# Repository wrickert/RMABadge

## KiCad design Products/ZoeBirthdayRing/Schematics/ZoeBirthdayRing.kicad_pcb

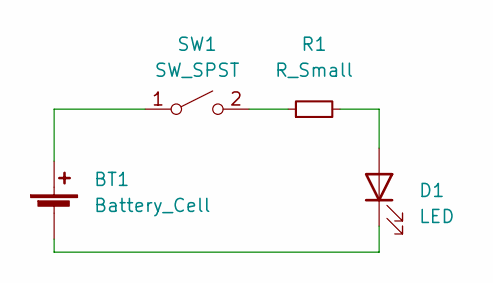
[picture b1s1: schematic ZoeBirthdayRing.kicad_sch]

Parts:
BT1: Battery_Cell; CR2032-MY-2032-12
D1: LED; RGBFlashLED
R1: R_Small; R_0805_2012Metric
SW1: SW_SPST; SW_SPDT_PCM12

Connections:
unnamed: BT1.1 (+), SW1.1 (A)
unnamed: BT1.2 (-), D1.1 (K)
unnamed: D1.2 (A), R1.2
unnamed: R1.1, SW1.2 (B)

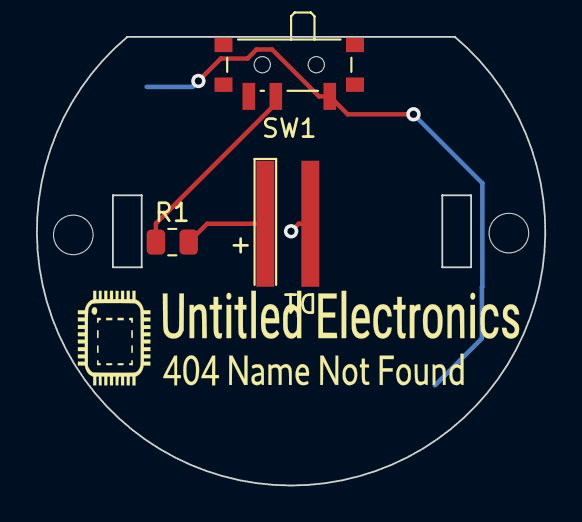
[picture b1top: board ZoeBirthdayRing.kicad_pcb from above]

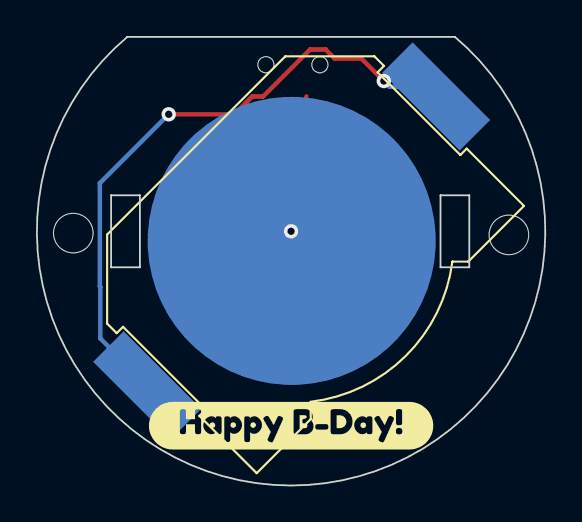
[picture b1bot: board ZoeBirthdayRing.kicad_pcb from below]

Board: 2 copper layers, 28.2 x 24.9 mm, 6 parts (2 on the bottom side), 4 nets.

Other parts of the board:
Ref**: Val**; UELogoSmall
kibuzzard-636FCE78: G***; kibuzzard-636FCE78

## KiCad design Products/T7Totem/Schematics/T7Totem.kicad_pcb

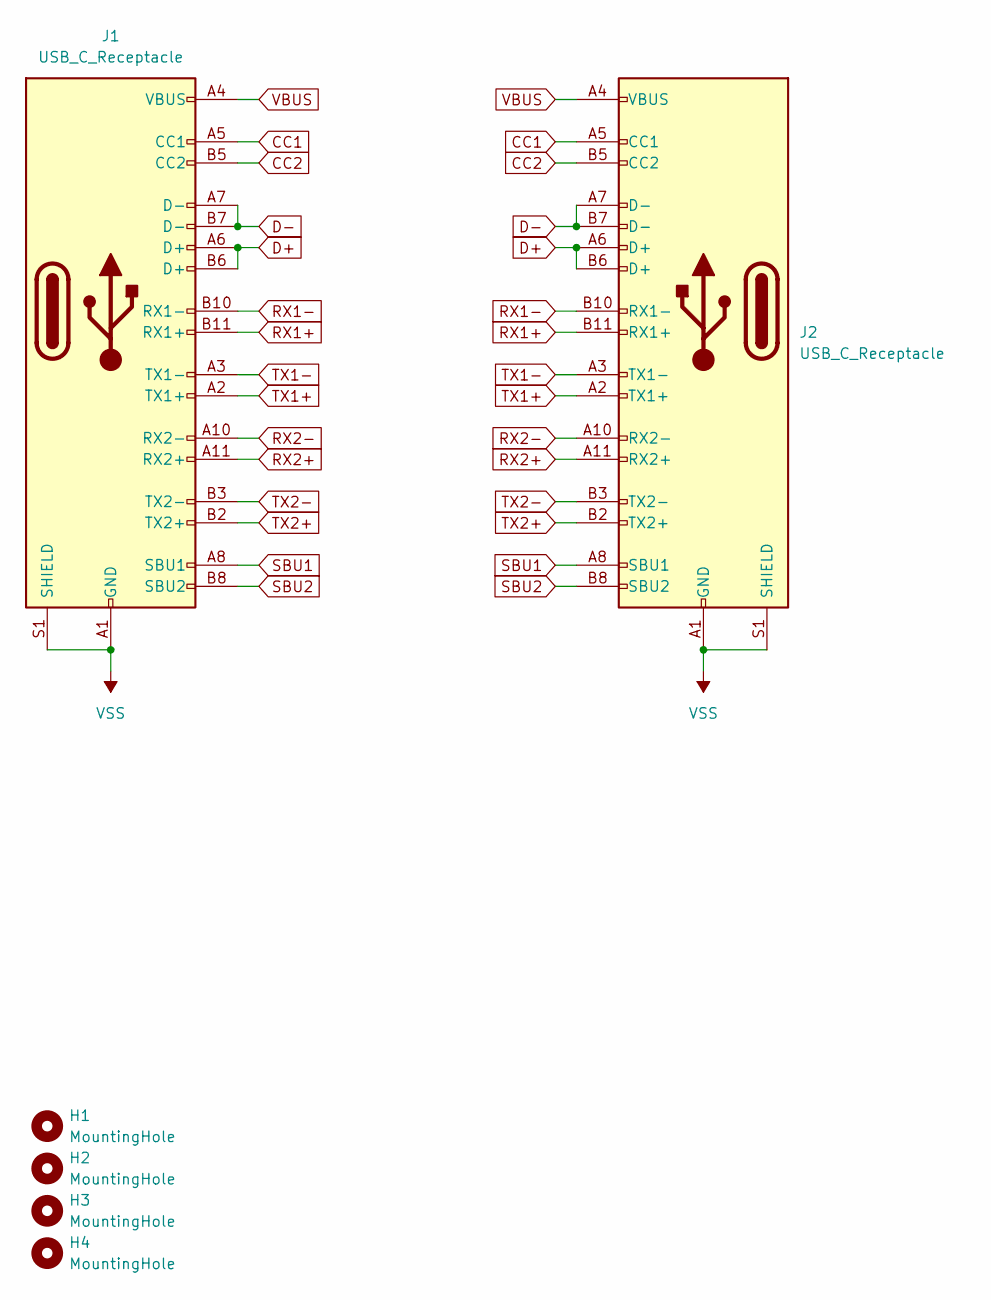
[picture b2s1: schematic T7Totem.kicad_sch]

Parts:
H1, H2, H3, H4: MountingHole; MountingHole_3.2mm_M3
J1: USB_C_Receptacle; U263-241N-4BQC15 Male USBC
J2: USB_C_Receptacle; TYPEC-324-BCP24 USBC Female

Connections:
CC1: J1.A5 (CC1), J2.A5 (CC1)
CC2: J1.B5 (CC2), J2.B5 (CC2)
D+: J1.A6 (D+), J1.B6 (D+), J2.A6 (D+), J2.B6 (D+)
D-: J1.A7 (D-), J1.B7 (D-), J2.A7 (D-), J2.B7 (D-)
RX1+: J1.B11 (RX1+), J2.B11 (RX1+)
RX1-: J1.B10 (RX1-), J2.B10 (RX1-)
RX2+: J1.A11 (RX2+), J2.A11 (RX2+)
RX2-: J1.A10 (RX2-), J2.A10 (RX2-)
SBU1: J1.A8 (SBU1), J2.A8 (SBU1)
SBU2: J1.B8 (SBU2), J2.B8 (SBU2)
TX1+: J1.A2 (TX1+), J2.A2 (TX1+)
TX1-: J1.A3 (TX1-), J2.A3 (TX1-)
TX2+: J1.B2 (TX2+), J2.B2 (TX2+)
TX2-: J1.B3 (TX2-), J2.B3 (TX2-)
VBUS: J1.A4 (VBUS), J1.A9 (VBUS), J1.B4 (VBUS), J1.B9 (VBUS), J2.A4 (VBUS), J2.A9 (VBUS), J2.B4 (VBUS), J2.B9 (VBUS)
VSS: J1.A1 (GND), J1.A12 (GND), J1.B1 (GND), J1.B12 (GND), J1.S1 (SHIELD), J2.A1 (GND), J2.A12 (GND), J2.B1 (GND), J2.B12 (GND), J2.S1 (SHIELD)

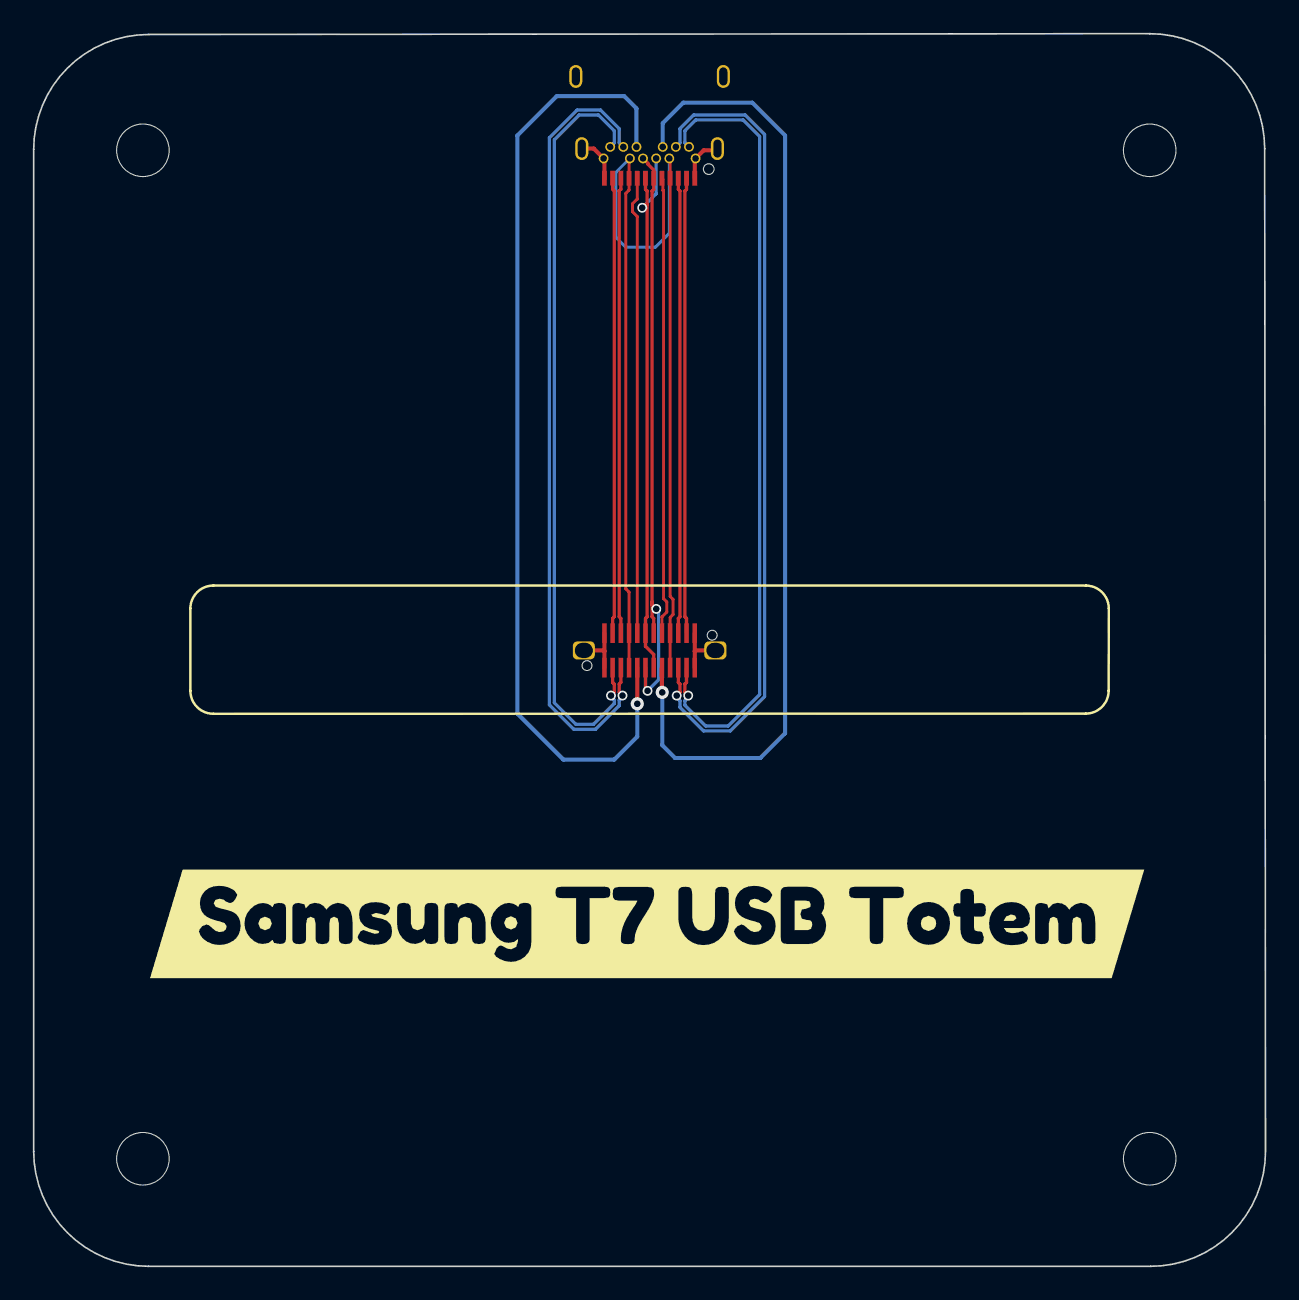
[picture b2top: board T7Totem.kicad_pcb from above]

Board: 4 copper layers, 75.0 x 75.1 mm, 7 parts (0 on the bottom side), 16 nets.

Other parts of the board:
kibuzzard-63322C6E: G***; kibuzzard-63322C6E

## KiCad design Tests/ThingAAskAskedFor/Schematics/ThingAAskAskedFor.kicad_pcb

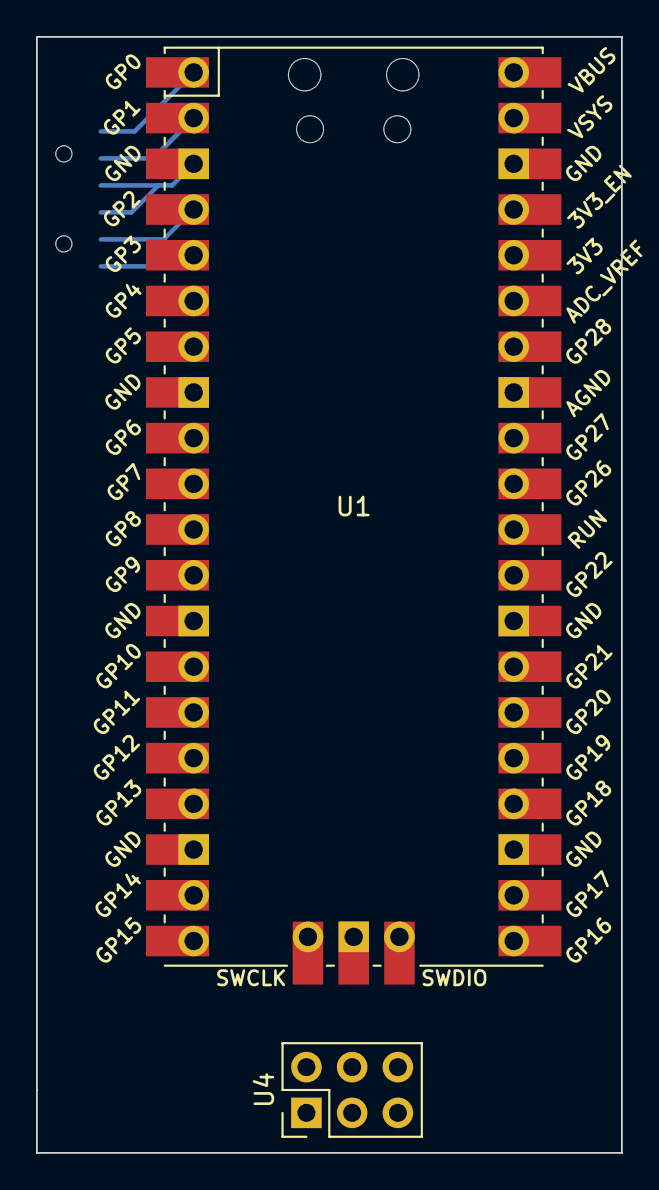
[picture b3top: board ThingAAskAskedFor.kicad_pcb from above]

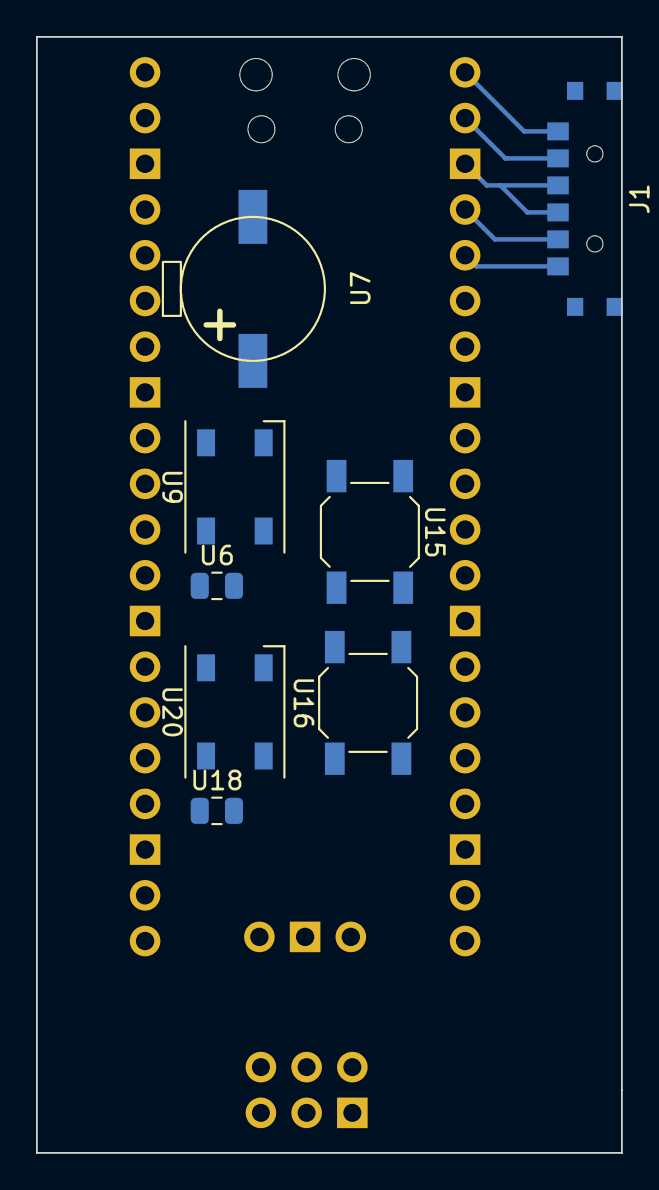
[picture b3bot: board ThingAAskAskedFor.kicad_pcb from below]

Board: 2 copper layers, 32.5 x 62.0 mm, 10 parts (8 on the bottom side), 9 nets.

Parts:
J1: Conn_01x06; MK-14C01-G2 SP4T Switch
U1: Pico; RPi_Pico_SMD_TH
U4: Conn_02x03_Odd_Even; PinHeader_2x03_P2.54mm_Vertical
U6, U18: 100nF; C_0805_2012Metric
U7: Buzzer; FUET-9032-Buzzer
U9, U20: SK6812; LED_SK6812_PLCC4_5.0x5.0mm_P3.2mm
U15, U16: SW_Push; SW_SPST_SKQG_WithoutStem

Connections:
1: J1.6, U1.1 (GPIO0)
2: J1.5, U1.2 (GPIO1)
3: J1.2, U1.4 (GPIO2)
4: J1.1, U1.5 (GPIO3)
Button1: U1.6 (GPIO4), U15.1
Button2: U1.7 (GPIO5), U16.1
unnamed: U9.4 (DOUT), U20.2 (DIN)
VCC: U4.2, U6.1, U9.3 (VDD), U18.1, U20.3 (VDD)
VSS: J1.3, J1.4, U1.3 (GND), U1.8 (GND), U1.13 (GND), U1.18 (GND), U1.23 (GND), U1.28 (GND), U1.33 (AGND), U1.38 (GND), U1.42 (GND), U4.1, U6.2, U7.2 (+), U9.1 (VSS), U15.2, U16.2, U18.2, U20.1 (VSS)

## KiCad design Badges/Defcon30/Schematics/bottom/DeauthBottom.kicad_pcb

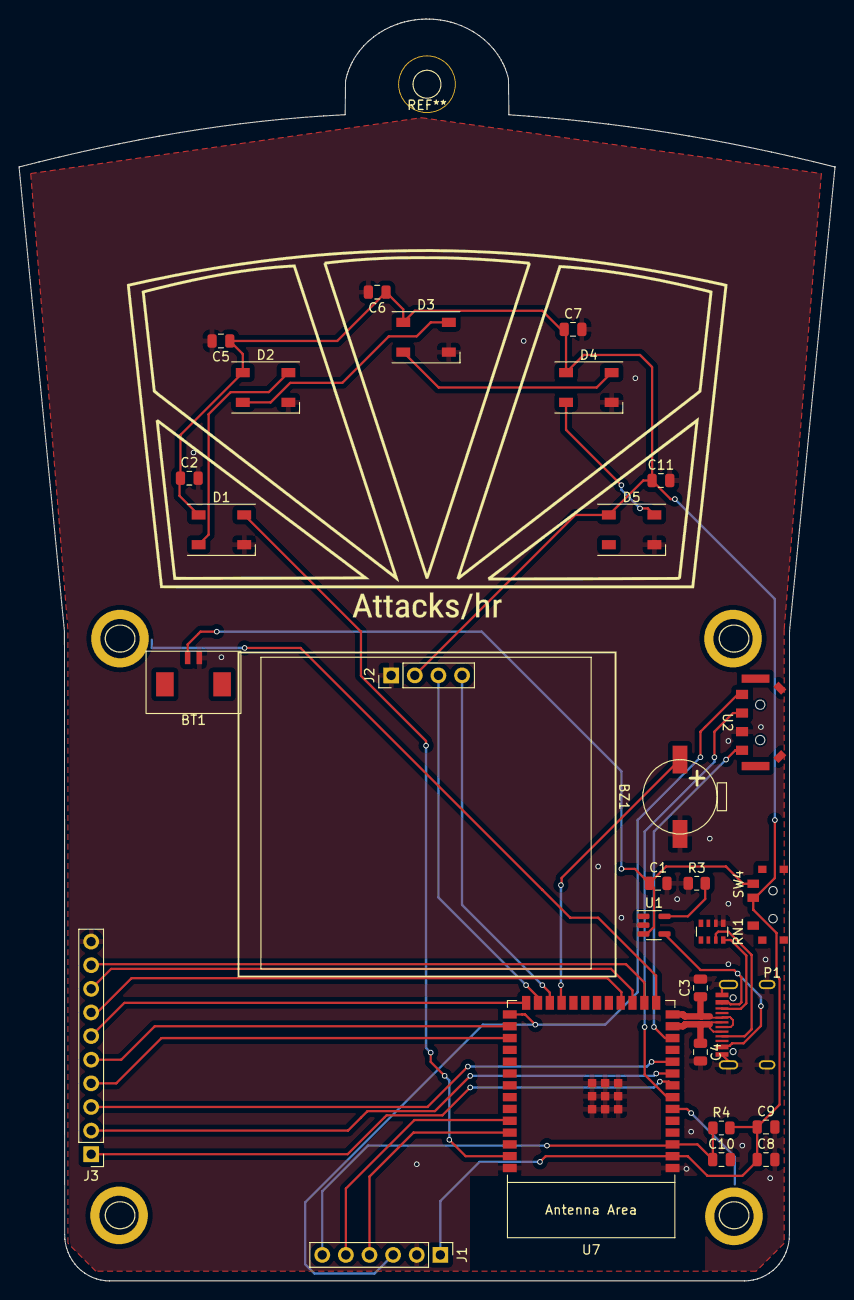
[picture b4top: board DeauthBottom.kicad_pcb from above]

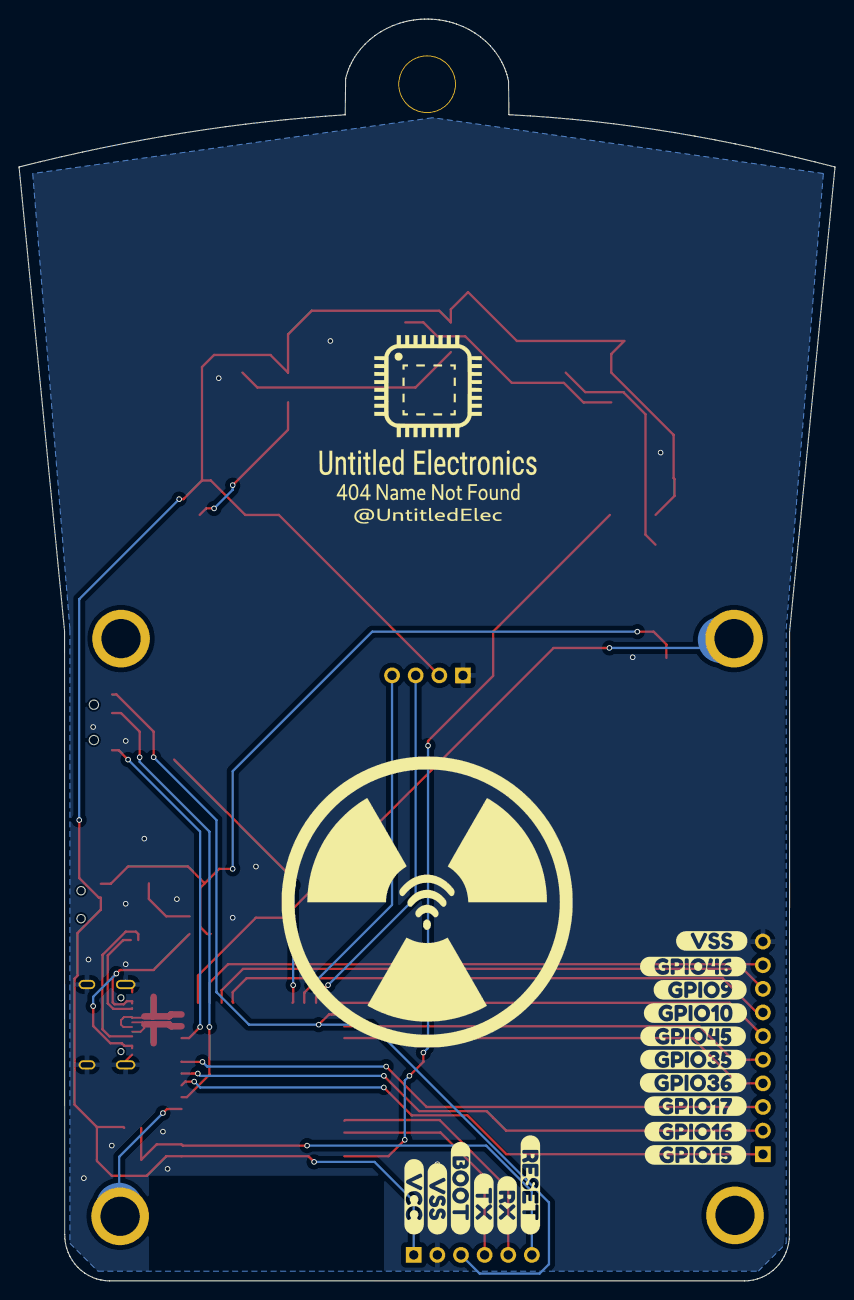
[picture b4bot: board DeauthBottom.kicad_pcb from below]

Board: 2 copper layers, 87.7 x 135.7 mm, 53 parts (20 on the bottom side), 33 nets.

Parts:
BT1: Battery_Cell; AFC12-S02DCC-00
BZ1: Buzzer; FUET-9032-Buzzer
C1: 10uF; C_0805_2012Metric
C2, C5, C6, C7, C9, C10, C11: 100nF; C_0805_2012Metric
C3, C4: 20pF; C_0805_2012Metric
C8: 22uF; C_0805_2012Metric
D1, D2, D3, D4, D5: SK6812; LED_SK6812_PLCC4_5.0x5.0mm_P3.2mm
J1: Program; PinHeader_1x06_P2.54mm_Vertical
J2: Oled Display; Oled
J3: Conn_01x10; PinHeader_1x10_P2.54mm_Vertical
J5, J6, J7, J8: Conn_01x01; SMD Spacer M2.5
J10, J13: Cap Sense; CapSense
P1: USB_C_Plug_corrected; USB_C_Receptical-Jing
R3: 2.5k; R_0805_2012Metric
R4: 1k; R_0805_2012Metric
RN1: 5.1k; R_Array_Convex_4x0603
Ref**: Val**; UELogoAbove
Ref**#2: Val**; wifiRadiation
SW4: SW_SPDT; SK-3296S_switch
U1: HX4055M; SOT-23-5
U2: TM-2023
U7: ESP32-S2-SOLO
kibuzzard-629CC9A4: G***; kibuzzard-629CC9A4
kibuzzard-629CC9AE: G***; kibuzzard-629CC9AE
kibuzzard-629CC9B7: G***; kibuzzard-629CC9B7
kibuzzard-629CC9C0: G***; kibuzzard-629CC9C0
kibuzzard-629CC968: G***; kibuzzard-629CC968
kibuzzard-629CC972: G***; kibuzzard-629CC972
kibuzzard-629CFC39: G***; kibuzzard-629CFC39
kibuzzard-629D3ABB: G***; kibuzzard-629D3ABB
kibuzzard-629D3AC7: G***; kibuzzard-629D3AC7
kibuzzard-629D3AD2: G***; kibuzzard-629D3AD2
kibuzzard-629D3AE1: G***; kibuzzard-629D3AE1
kibuzzard-629D3AEB: G***; kibuzzard-629D3AEB
kibuzzard-629D3AFA: G***; kibuzzard-629D3AFA
kibuzzard-629D3B0B: G***; kibuzzard-629D3B0B
kibuzzard-629D3B1D: G***; kibuzzard-629D3B1D
kibuzzard-629D3B73: G***; kibuzzard-629D3B73

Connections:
1: J3.1, U7.8 (GPIO15/U0RTS/ADC2_CH4/XTAL_32K_P)
2: J3.2, U7.9 (GPIO16/U0CTS/ADC2_CH5/XTAL_32K_N)
3: J3.3, U7.10 (GPIO17/U1TXD/ADC2_CH6/DAC_1)
5: J3.6, U7.26 (GPIO45)
6: J3.9, U7.16 (GPIO46)
7: J3.7, U7.18 (GPIO10/TOUCH10/ADC1_CH9/FSPICS0/FSPIIO4)
8: J3.8, U7.17 (GPIO9/TOUCH9/ADC1_CH8/FSPIHD)
9: J3.5, U7.28 (SPIIO6/GPIO35/FSPID)
10: J3.4, U7.29 (SPIIO7/GPIO36/FSPICLK)
/D+: C3.1, P1.A6 (D+), P1.B6 (D+), U7.14 (GPIO20/U1CTS/ADC2_CH9/CLK_OUT1/USB_D+)
/D-: C4.1, P1.A7 (D-), P1.B7 (D-), U7.13 (GPIO19/U1RTS/ADC2_CH8/CLK_OUT2/USB_D-)
/SCL: J2.3, U7.25 (SPIIO5/GPIO34/FSPICS0)
/SDA: J2.4, U7.24 (SPIIO4/GPIO33/FSPIHD)
/SK6812: D1.2 (DIN), U7.39 (GPIO1/TOUCH1/ADC1_CH0)
Buzzer: BZ1.1 (-), U7.23 (GPIO21)
Down: U2.4 (2), U7.12 (GPIO8/TOUCH8/ADC1_CH7)
unnamed: D1.4 (DOUT), D2.2 (DIN)
unnamed: D2.4 (DOUT), D3.2 (DIN)
unnamed: D3.4 (DOUT), D4.2 (DIN)
unnamed: D4.4 (DOUT), D5.2 (DIN)
unnamed: J10.1, U7.15 (GPIO3/TOUCH3/ADC1_CH2)
unnamed: J13.1, U7.6 (GPIO6/TOUCH6/ADC1_CH5)
unnamed: P1.A5 (CC), RN1.7 (R2.2)
unnamed: P1.B5 (VCONN), RN1.8 (R1.2)
unnamed: R3.2, U1.5 (PROG)
RX: J1.5, U7.36 (U0RXD/GPIO44/CLK_OUT2)
Reset: C10.1, J1.6, R4.1, U7.3 (EN)
TX: J1.4, U7.37 (U0TXD/GPIO43/CLK_OUT1)
Up: J1.3, U2.1, U7.27 (GPIO0)
VBUS: P1.A4 (VBUS), P1.A9 (VBUS), P1.B4 (VBUS), P1.B9 (VBUS), U1.4 (VCC)
VCC: C2.1, C5.1, C6.1, C7.1, C8.1, C9.1, C11.1, D1.3 (VDD), D2.3 (VDD), D3.3 (VDD), D4.3 (VDD), D5.3 (VDD), J1.1, J2.2, R4.2, SW4.2 (B), U7.2 (3V3)
VDDA: BT1.1 (+), C1.1, SW4.1 (A), U1.3 (Bat)
VSS: BT1.2 (-), BZ1.2 (+), C1.2, C2.2, C3.2, C4.2, C5.2, C6.2, C7.2, C8.2, C9.2, C10.2, C11.2, D1.1 (VSS), D2.1 (VSS), D3.1 (VSS), D4.1 (VSS), D5.1 (VSS), J1.2, J2.1, J3.10, P1.A1 (GND), P1.A12 (GND), P1.B1 (GND), P1.B12 (GND), P1.S1 (SHIELD), R3.1, RN1.1 (R1.1), RN1.2 (R2.1), U1.2 (Gnd), U2.C, U7.1 (GND), U7.40 (GND), U7.41 (GND)

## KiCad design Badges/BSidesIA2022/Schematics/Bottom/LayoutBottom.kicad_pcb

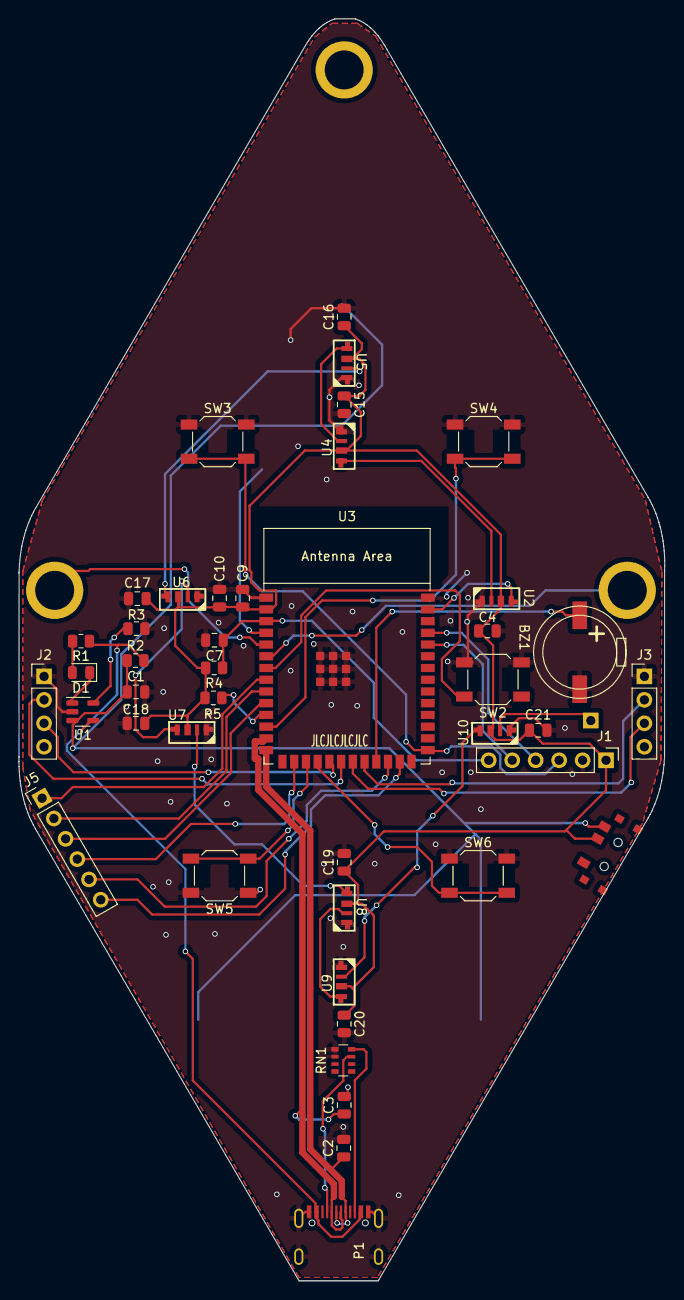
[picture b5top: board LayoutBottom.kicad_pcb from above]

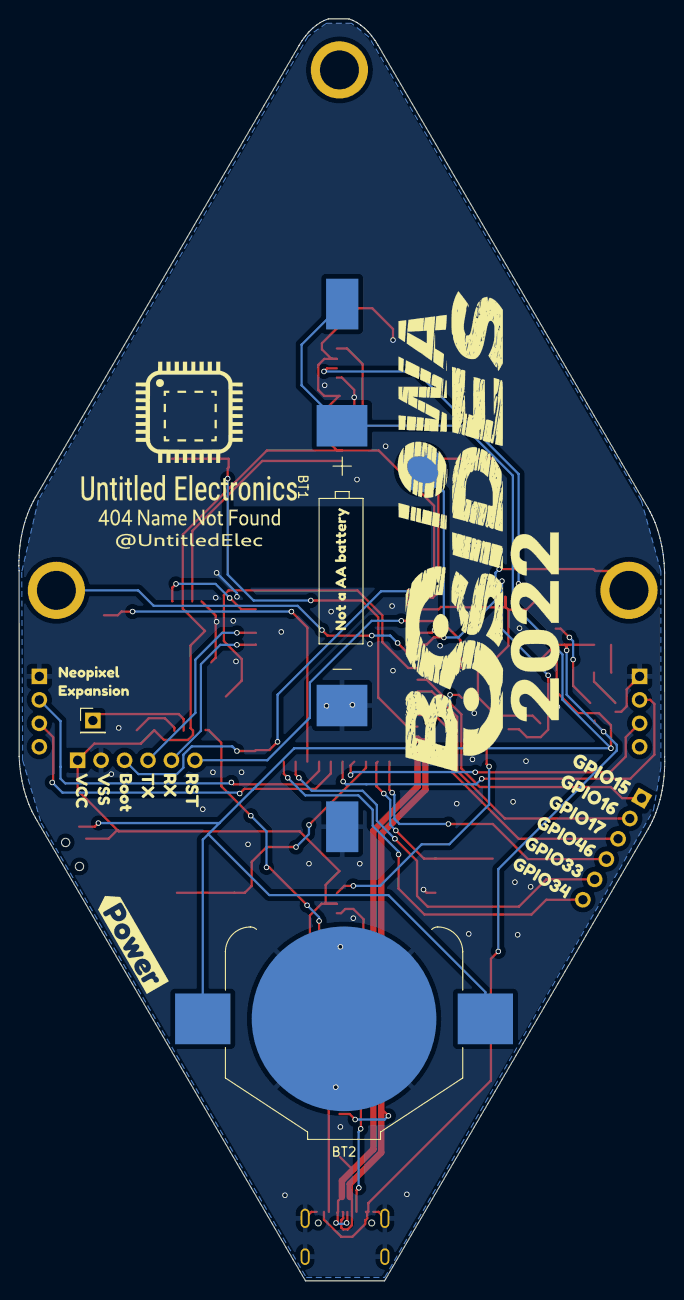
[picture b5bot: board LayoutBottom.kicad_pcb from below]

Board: 2 copper layers, 69.9 x 136.6 mm, 59 parts (11 on the bottom side), 43 nets.

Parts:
BT1: Battery_Cell; Dongguan14500
BT2: Battery_Cell; BatteryHolder_Keystone_3008_1x2450
BZ1: Buzzer; FUET-9032-Buzzer
C1: 10uF; C_0805_2012Metric
C2, C3: 20pF; C_0805_2012Metric
C4, C7, C9, C15, C16, C17, C18, C19, C20, C21: 100nF; C_0805_2012Metric
C10: 22uF; C_0805_2012Metric
D1: LED DNP; LED_0805_2012Metric
J1: Program; PinHeader_1x06_P2.54mm_Vertical
J2: Left_IN; PinHeader_1x04_P2.54mm_Vertical
J3: Right_Out; PinHeader_1x04_P2.54mm_Vertical
J5: Conn_01x06; PinHeader_1x06_P2.54mm_Vertical
J6, J8, J9: Conn_01x01; SMD Spacer M2.5
J11, J12, J13: Cap Sense; CapSense
J14: Neopixel Expansion; PinHeader_1x01_P2.54mm_Vertical
P1: USB_C_Plug_corrected; USB_C_Receptical-Jing
R1: 1k DNP; R_0805_2012Metric
R2: Charger Bypass DNP; R_0805_2012Metric
R3: 2.5k; R_0805_2012Metric
R4: 1k; R_0805_2012Metric
R5: 10k DNP; R_0805_2012Metric
RN1: 5.1k; R_Array_Convex_4x0603
Ref**: Val**; UELogoAbove
Ref**#2: Val**; BackLogo
SW1: SW_SPDT; SK-3296S_switch
SW2, SW3, SW4, SW5, SW6: SW_Push; SW_SPST_SKQG_WithoutStem
U1: HX4055M; SOT-23-5
U2, U4, U5, U6, U7, U8, U9, U10: SK6812_Side
U3: ESP32-S2-SOLO
kibuzzard-623F4E8E: G***; kibuzzard-623F4E8E
kibuzzard-623F47EC: G***; kibuzzard-623F47EC
kibuzzard-623F48F6: G***; kibuzzard-623F48F6
kibuzzard-623F49DD: G***; kibuzzard-623F49DD
kibuzzard-623F4981: G***; kibuzzard-623F4981

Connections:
1: J5.1, U3.8 (GPIO15/U0RTS/ADC2_CH4/XTAL_32K_P)
2: J5.2, U3.9 (GPIO16/U0CTS/ADC2_CH5/XTAL_32K_N)
3: J5.3, U3.10 (GPIO17/U1TXD/ADC2_CH6/DAC_1)
6: J5.4, U3.16 (GPIO46)
7: J5.5, U3.24 (SPIIO4/GPIO33/FSPIHD)
8: J5.6, U3.25 (SPIIO5/GPIO34/FSPICS0)
/D+: C2.1, P1.A6 (D+), P1.B6 (D+), U3.14 (GPIO20/U1CTS/ADC2_CH9/CLK_OUT1/USB_D+)
/D-: C3.1, P1.A7 (D-), P1.B7 (D-), U3.13 (GPIO19/U1RTS/ADC2_CH8/CLK_OUT2/USB_D-)
/SK6812: U2.1 (Din), U3.39 (GPIO1/TOUCH1/ADC1_CH0)
BottomLeft: SW5.2, U3.17 (GPIO9/TOUCH9/ADC1_CH8/FSPIHD)
BottomRight: SW6.2, U3.18 (GPIO10/TOUCH10/ADC1_CH9/FSPICS0/FSPIIO4)
Buzzer: BZ1.1 (-), U3.23 (GPIO21)
Extra: SW2.1, U3.7 (GPIO7/TOUCH7/ADC1_CH6)
LeftOne: J2.3, U3.19 (GPIO11/TOUCH11/ADC2_CH0/FSPID/FSPIIO5)
LeftTwo: J2.2, U3.20 (GPIO12/TOUCH12/ADC2_CH1/FSPICLK/FSPIIO6)
unnamed: D1.2 (A), R1.1
unnamed: D1.1 (K), U1.1 (Chrg)
unnamed: J11.1, U3.4 (GPIO4/TOUCH4/ADC1_CH3)
unnamed: J9.1, J12.1, U3.5 (GPIO5/TOUCH5/ADC1_CH4)
unnamed: J8.1, J13.1, U3.6 (GPIO6/TOUCH6/ADC1_CH5)
unnamed: J14.1, U10.3 (Dout)
unnamed: P1.A5 (CC), RN1.7 (R2.2)
unnamed: P1.B5 (VCONN), RN1.8 (R1.2)
unnamed: R3.2, U1.5 (PROG)
unnamed: U2.3 (Dout), U4.1 (Din)
unnamed: R5.2, U3.11 (GPIO18/U1RXD/ADC2_CH7/DAC_2/CLK_OUT3)
unnamed: U4.3 (Dout), U5.1 (Din)
unnamed: U5.3 (Dout), U6.1 (Din)
unnamed: U6.3 (Dout), U7.1 (Din)
unnamed: U7.3 (Dout), U8.1 (Din)
unnamed: U8.3 (Dout), U9.1 (Din)
unnamed: U9.3 (Dout), U10.1 (Din)
RX: J1.5, U3.36 (U0RXD/GPIO44/CLK_OUT2)
Reset: C7.1, J1.6, R4.1, U3.3 (EN)
RightOne: J3.3, U3.21 (GPIO13/TOUCH13/ADC2_CH2/FSPIQ/FSPIIO7)
RightTwo: J3.2, U3.22 (GPIO14/TOUCH14/ADC2_CH3/FSPIWP/FSPIDQS)
TX: J1.4, U3.37 (U0TXD/GPIO43/CLK_OUT1)
TopLeft: J1.3, SW3.2, U3.27 (GPIO0)
TopRight: SW4.2, U3.12 (GPIO8/TOUCH8/ADC1_CH7)
VBUS: P1.A4 (VBUS), P1.A9 (VBUS), P1.B4 (VBUS), P1.B9 (VBUS), R1.2, R2.1, U1.4 (VCC)
VCC: C4.1, C9.1, C10.1, C15.1, C16.1, C17.1, C18.1, C19.1, C20.1, C21.1, J1.1, R4.2, R5.1, SW1.2 (B), U2.2 (VCC), U3.2 (3V3), U4.2 (VCC), U5.2 (VCC), U6.2 (VCC), U7.2 (VCC), U8.2 (VCC), U9.2 (VCC), U10.2 (VCC)
VDDA: BT1.1 (+), BT2.1 (+), C1.1, R2.2, SW1.1 (A), U1.3 (Bat)
VSS: BT1.2 (-), BT2.2 (-), BZ1.2 (+), C1.2, C2.2, C3.2, C4.2, C7.2, C9.2, C10.2, C15.2, C16.2, C17.2, C18.2, C19.2, C20.2, C21.2, J1.2, J2.1, J3.1, P1.A1 (GND), P1.A12 (GND), P1.B1 (GND), P1.B12 (GND), P1.S1 (SHIELD), R3.1, RN1.1 (R1.1), RN1.2 (R2.1), SW2.2, SW3.1, SW4.1, SW5.1, SW6.1, U1.2 (Gnd), U2.4 (GND), U3.1 (GND), U3.40 (GND), U3.41 (GND), U4.4 (GND), U5.4 (GND), U6.4 (GND), U7.4 (GND), U8.4 (GND), U9.4 (GND), U10.4 (GND)

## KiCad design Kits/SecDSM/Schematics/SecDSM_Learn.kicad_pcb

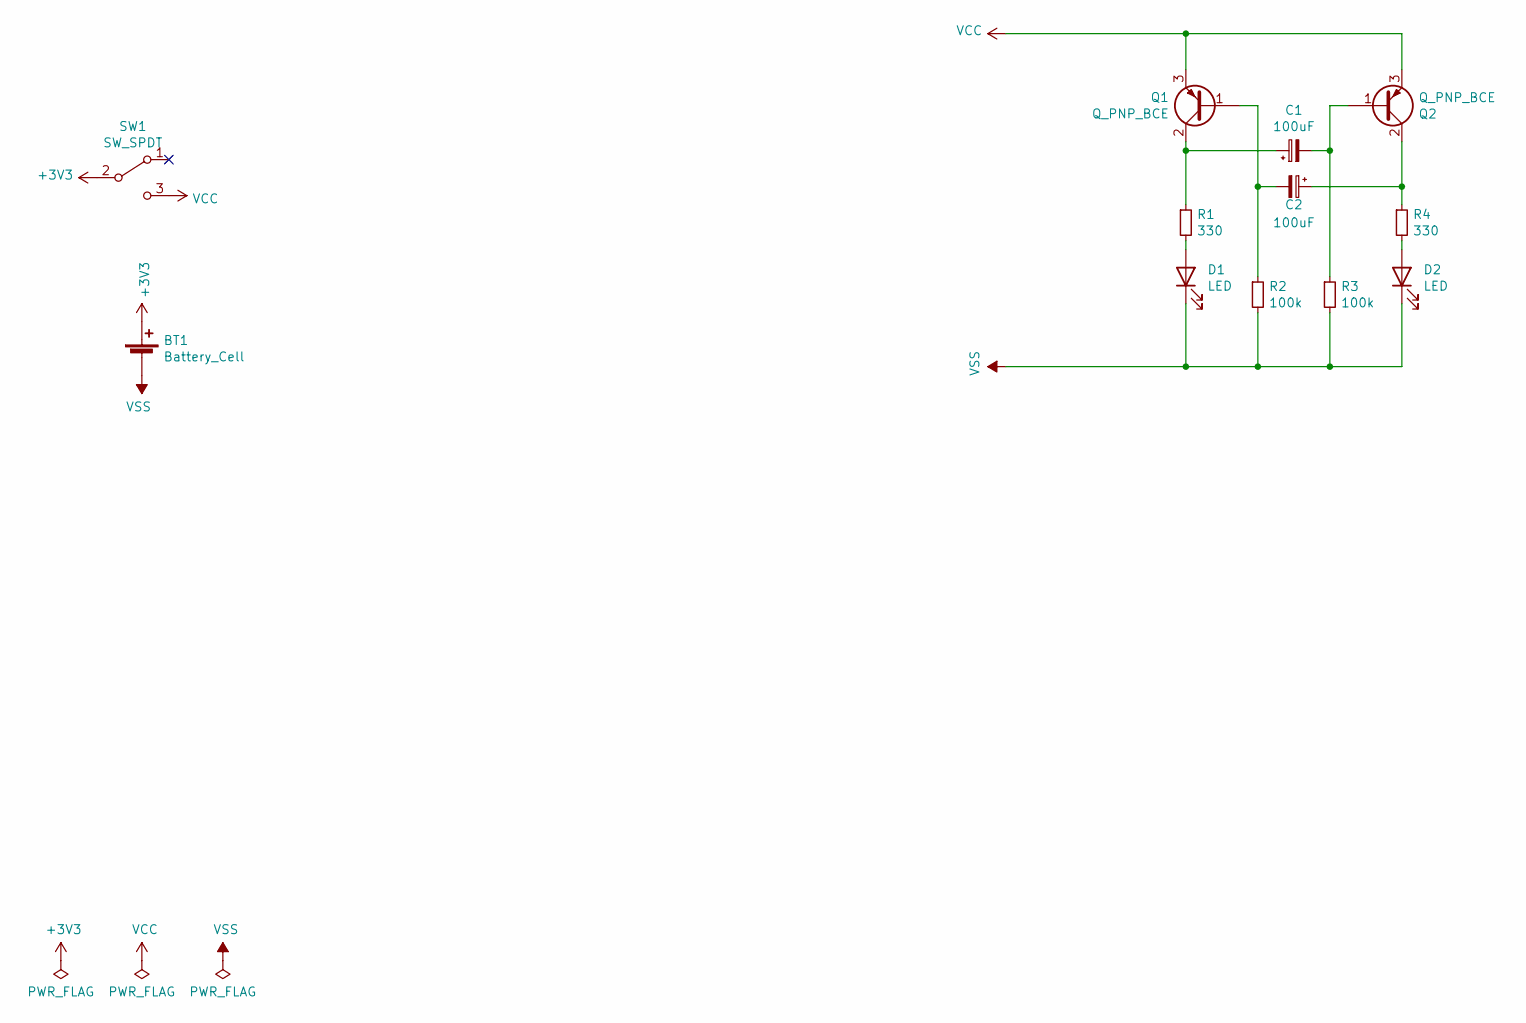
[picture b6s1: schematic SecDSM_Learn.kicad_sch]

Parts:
BT1: Battery_Cell; BatteryHolder_MPD_BC2003_1x2032
C1, C2: 100uF; C_1206_3216Metric
D1, D2: LED; LED_0805_2012Metric
Q1, Q2: Q_PNP_BCE; SOT-23
R1, R4: 330; R_0805_2012Metric
R2, R3: 100k; R_0805_2012Metric
SW1: SW_SPDT; SK-3296S_switch

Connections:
+3V3: BT1.1 (+), SW1.2 (B)
unnamed: C1.1, Q1.2 (C), R1.1
unnamed: C1.2, Q2.1 (B), R3.1
unnamed: C2.1, Q2.2 (C), R4.1
unnamed: C2.2, Q1.1 (B), R2.1
unnamed: D1.2 (A), R1.2
unnamed: D2.2 (A), R4.2
VCC: Q1.3 (E), Q2.3 (E), SW1.3 (C)
VSS: BT1.2 (-), D1.1 (K), D2.1 (K), R2.2, R3.2

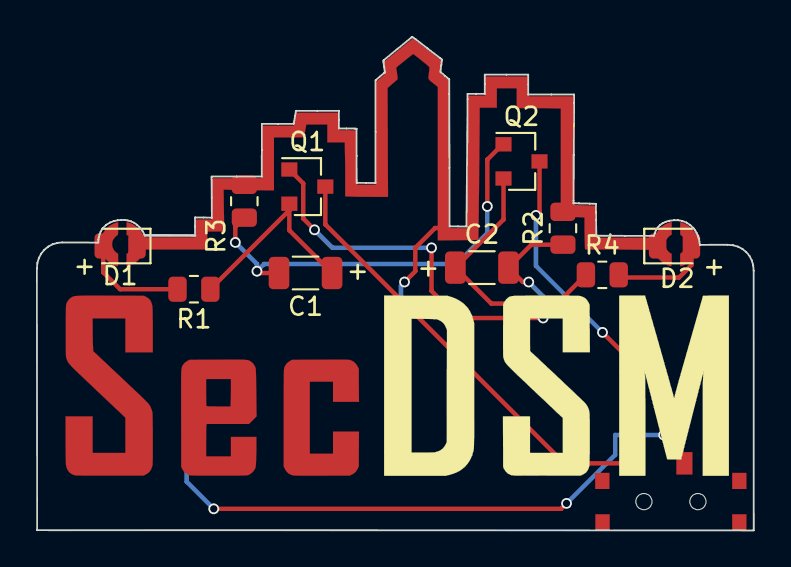
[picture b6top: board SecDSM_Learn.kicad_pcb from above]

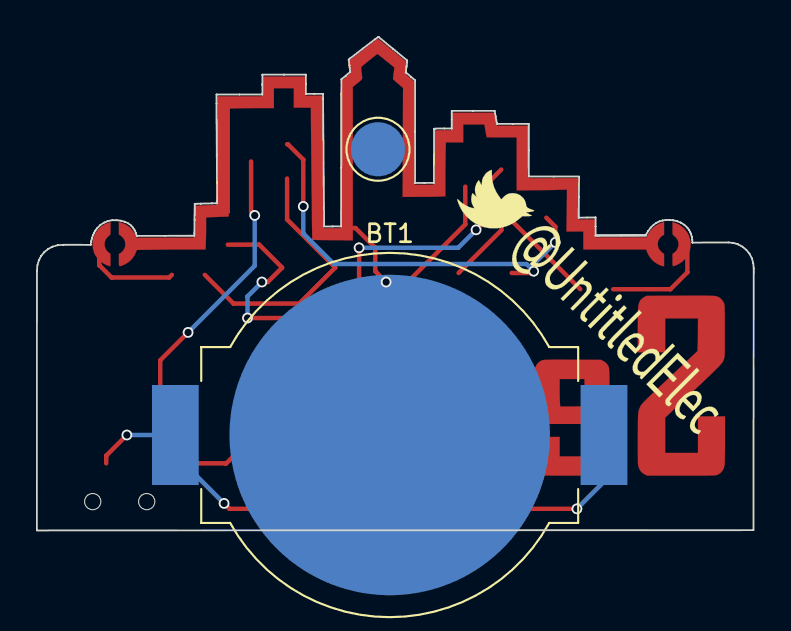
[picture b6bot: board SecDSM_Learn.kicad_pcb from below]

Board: 2 copper layers, 39.8 x 27.4 mm, 13 parts (2 on the bottom side), 9 nets.

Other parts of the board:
Ref**: Val**; TwitterSmaller

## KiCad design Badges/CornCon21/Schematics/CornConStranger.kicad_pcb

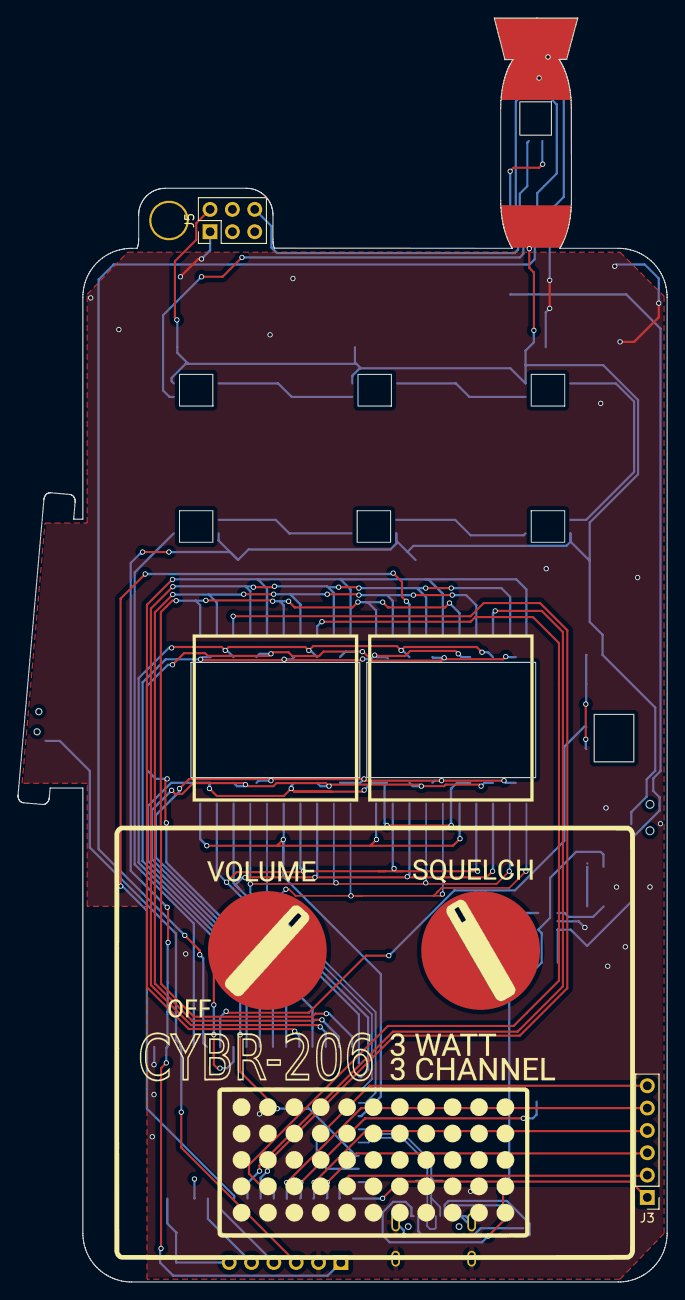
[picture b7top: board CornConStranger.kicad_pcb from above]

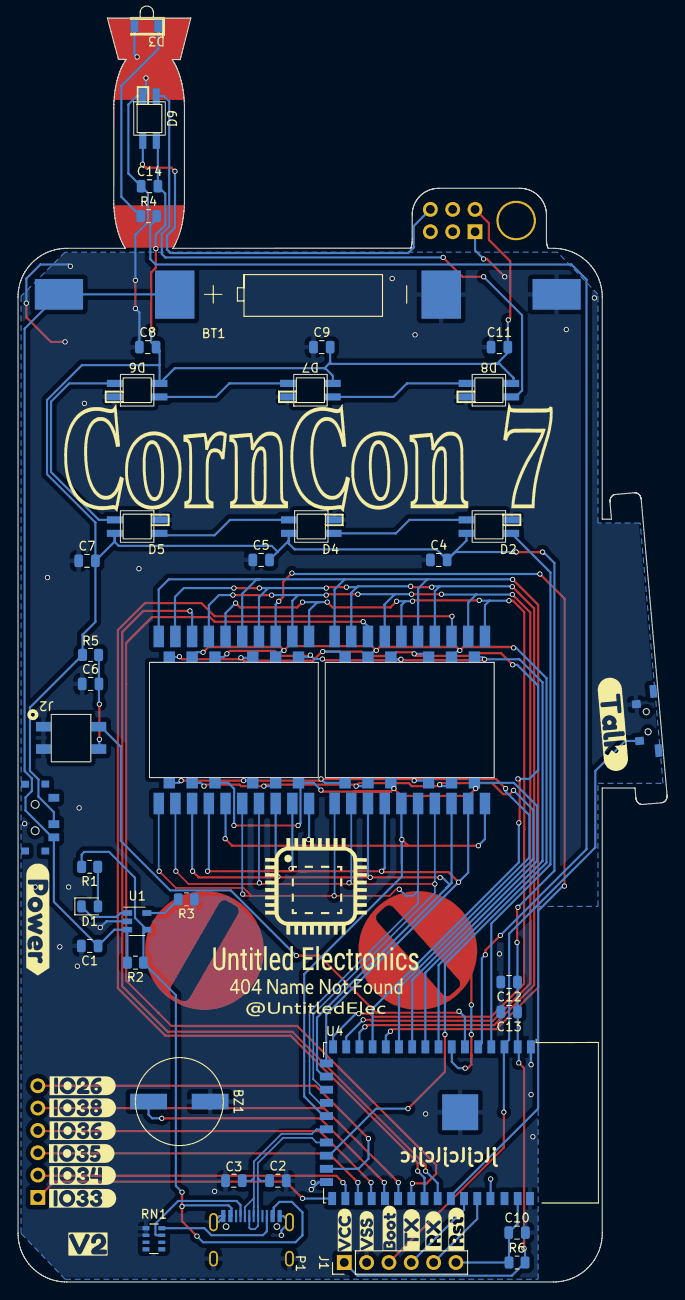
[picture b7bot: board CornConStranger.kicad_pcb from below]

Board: 2 copper layers, 73.8 x 143.7 mm, 60 parts (55 on the bottom side), 54 nets.

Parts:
BT1: Battery_Cell; Dongguan14500
BZ1: Buzzer; FUET-1030-3V-Buzzer
C1: 10uF; C_0805_2012Metric
C2, C3: 20pF; C_0805_2012Metric
C4, C5, C7, C8, C9, C10, C11, C12, C14: 100nF; C_0805_2012Metric
C6: C_Small; C_0805_2012Metric
C13: 22uF; C_0805_2012Metric
D1: LED_Small; LED_0805_2012Metric
D2, D4, D5, D6, D7, D8, D9: WS2812B; SK6812-E_Reverse
D3: LED_Small; IR26-61C
J1: Program; PinHeader_1x06_P2.54mm_Vertical
J2: IR Rx; IRM-H936
J3: Conn_01x06; PinHeader_1x06_P2.54mm_Vertical
J4: Cap Sense; CapSence
J5: Conn_02x03_Odd_Even; PinHeader_2x03_P2.54mm_Vertical
P1: USB_C_Plug_corrected; USB_C_Receptical-Jing
R1, R6: 1k; R_0805_2012Metric
R2: Charger Bypass; R_0805_2012Metric
R3, R4: R_Small; R_0805_2012Metric
R5: 47-220 Ohm; R_0805_2012Metric
RN1: 5.1k; R_Array_Convex_4x0603
Ref**: Val**; UELogoAbove
SW1: SW_SPDT; SK-3296S_switch
SW2: SW_DIP_x01; TS36CA-0.7-Button
U1: HX4055M; SOT-23-5
U2, U3: 14Seg; JSS-4021AUR-21-14Seg
U4: ESP32-S2-WROVER
svg2mod, svg2mod#2, svg2mod#3, svg2mod#4, svg2mod#5, svg2mod#6, svg2mod#7, svg2mod#8, svg2mod#9, svg2mod#10, svg2mod#11, svg2mod#12, svg2mod#13, svg2mod#14, svg2mod#15: G***; svg2mod

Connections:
1: J3.1, U4.27 (IO33)
2: J3.2, U4.28 (IO34)
3: J3.3, U4.29 (IO35)
4: J3.4, U4.30 (IO36)
6: J3.5, U4.32 (IO38)
7: J3.6, U4.25 (IO26)
/D+: C2.1, P1.A6 (D+), P1.B6 (D+), U4.23 (USB_D+)
/D-: C3.1, P1.A7 (D-), P1.B7 (D-), U4.22 (USB_D-)
/SK6812: D2.4 (DIN), U4.4 (IO01)
Boot: J1.3, SW2.1, U4.3 (IO00)
Buzzer: BZ1.1 (-), U4.31 (IO37)
Cout: D9.2 (DOUT), J5.6
IR Rx: J2.3, U4.6 (IO03)
IR Tx: R4.2, U4.5 (IO02)
unnamed: C6.2, J2.4, R5.1
unnamed: D1.1 (K), U1.1 (Chrg)
unnamed: D1.2 (A), R1.1
unnamed: D2.2 (DOUT), D4.4 (DIN)
unnamed: D3.2 (A), R4.1
unnamed: D4.2 (DOUT), D5.4 (DIN)
unnamed: D5.2 (DOUT), D6.4 (DIN)
unnamed: D6.2 (DOUT), D7.4 (DIN)
unnamed: D7.2 (DOUT), D8.4 (DIN)
unnamed: D8.2 (DOUT), D9.4 (DIN)
unnamed: J4.1, U4.7 (IO04)
unnamed: P1.A5 (CC), RN1.7 (R2.2)
unnamed: P1.B5 (VCONN), RN1.8 (R1.2)
unnamed: R3.2, U1.5 (PROG)
RX: J1.5, U4.38 (RXD0)
Reset: C10.1, J1.6, R6.1, U4.41 (EN)
SegA: U2.18 (A), U2.21 (A2), U3.18 (A), U3.21 (A2), U4.24 (IO21)
SegB: U2.19 (B), U2.22 (B2), U3.19 (B), U3.22 (B2), U4.13 (IO10)
SegC: U2.11 (C2), U2.14 (C), U3.11 (C2), U3.14 (C), U4.11 (IO08)
SegD: U2.12 (D2), U2.15 (D), U3.12 (D2), U3.15 (D), U4.10 (IO07)
SegDP: U2.5 (DP), U2.10 (DP2), U3.5 (DP), U3.10 (DP2), U4.20 (IO17)
SegE: U2.13 (E2), U2.16 (E), U3.13 (E2), U3.16 (E), U4.9 (IO06)
SegF: U2.27 (F2), U2.32 (F), U3.27 (F2), U3.32 (F), U4.16 (IO13)
SegG: U2.17 (G), U2.20 (G2), U3.17 (G), U3.20 (G2), U4.8 (IO05)
SegG1: U2.30 (G1), U4.34 (IO40)
SegG2: U2.25 (G2), U4.33 (IO39)
SegG3: U3.30 (G1), U4.36 (IO42)
SegG4: U3.25 (G2), U4.35 (IO41)
SegH: U2.26 (H2), U2.31 (H), U3.26 (H2), U3.31 (H), U4.15 (IO12)
SegJ: U2.24 (J2), U2.29 (J), U3.24 (J2), U3.29 (J), U4.14 (IO11)
SegK: U2.23 (K2), U2.28 (K), U3.23 (K2), U3.28 (K), U4.12 (IO09)
SegL: U2.4 (L), U2.9 (L2), U3.4 (L), U3.9 (L2), U4.19 (IO16)
SegM: U2.3 (M), U2.8 (M2), U3.3 (M), U3.8 (M2), U4.18 (IO15)
SegN: U2.2 (N), U2.7 (N2), U3.2 (N), U3.7 (N2), U4.17 (IO14)
SegP: U2.1, U2.6 (P2), U3.1, U3.6 (P2), U4.21 (IO18)
TX: J1.4, U4.37 (TXD0)
VBUS: P1.A4 (VBUS), P1.A9 (VBUS), P1.B4 (VBUS), P1.B9 (VBUS), R1.2, R2.1, U1.4 (VCC)
VCC: C4.2, C5.2, C7.2, C8.2, C9.2, C11.2, C12.1, C13.1, C14.2, D2.1 (VDD), D4.1 (VDD), D5.1 (VDD), D6.1 (VDD), D7.1 (VDD), D8.1 (VDD), D9.1 (VDD), J1.1, J5.2, R5.2, R6.2, SW1.2 (B), U4.2 (3V3)
VDDA: BT1.1 (+), C1.1, R2.2, SW1.1 (A), U1.3 (Bat)
VSS: BT1.2 (-), BZ1.2 (+), C1.2, C2.2, C3.2, C4.1, C5.1, C6.1, C7.1, C8.1, C9.1, C10.2, C11.1, C12.2, C13.2, C14.1, D2.3 (VSS), D3.1 (K), D4.3 (VSS), D5.3 (VSS), D6.3 (VSS), D7.3 (VSS), D8.3 (VSS), D9.3 (VSS), J1.2, J2.1, J2.2, J5.1, P1.A1 (GND), P1.A12 (GND), P1.B1 (GND), P1.B12 (GND), P1.S1 (SHIELD), R3.1, RN1.1 (R1.1), RN1.2 (R2.1), SW2.2, U1.2 (Gnd), U4.1 (GND), U4.26 (GND), U4.42 (GND), U4.43 (GND)
